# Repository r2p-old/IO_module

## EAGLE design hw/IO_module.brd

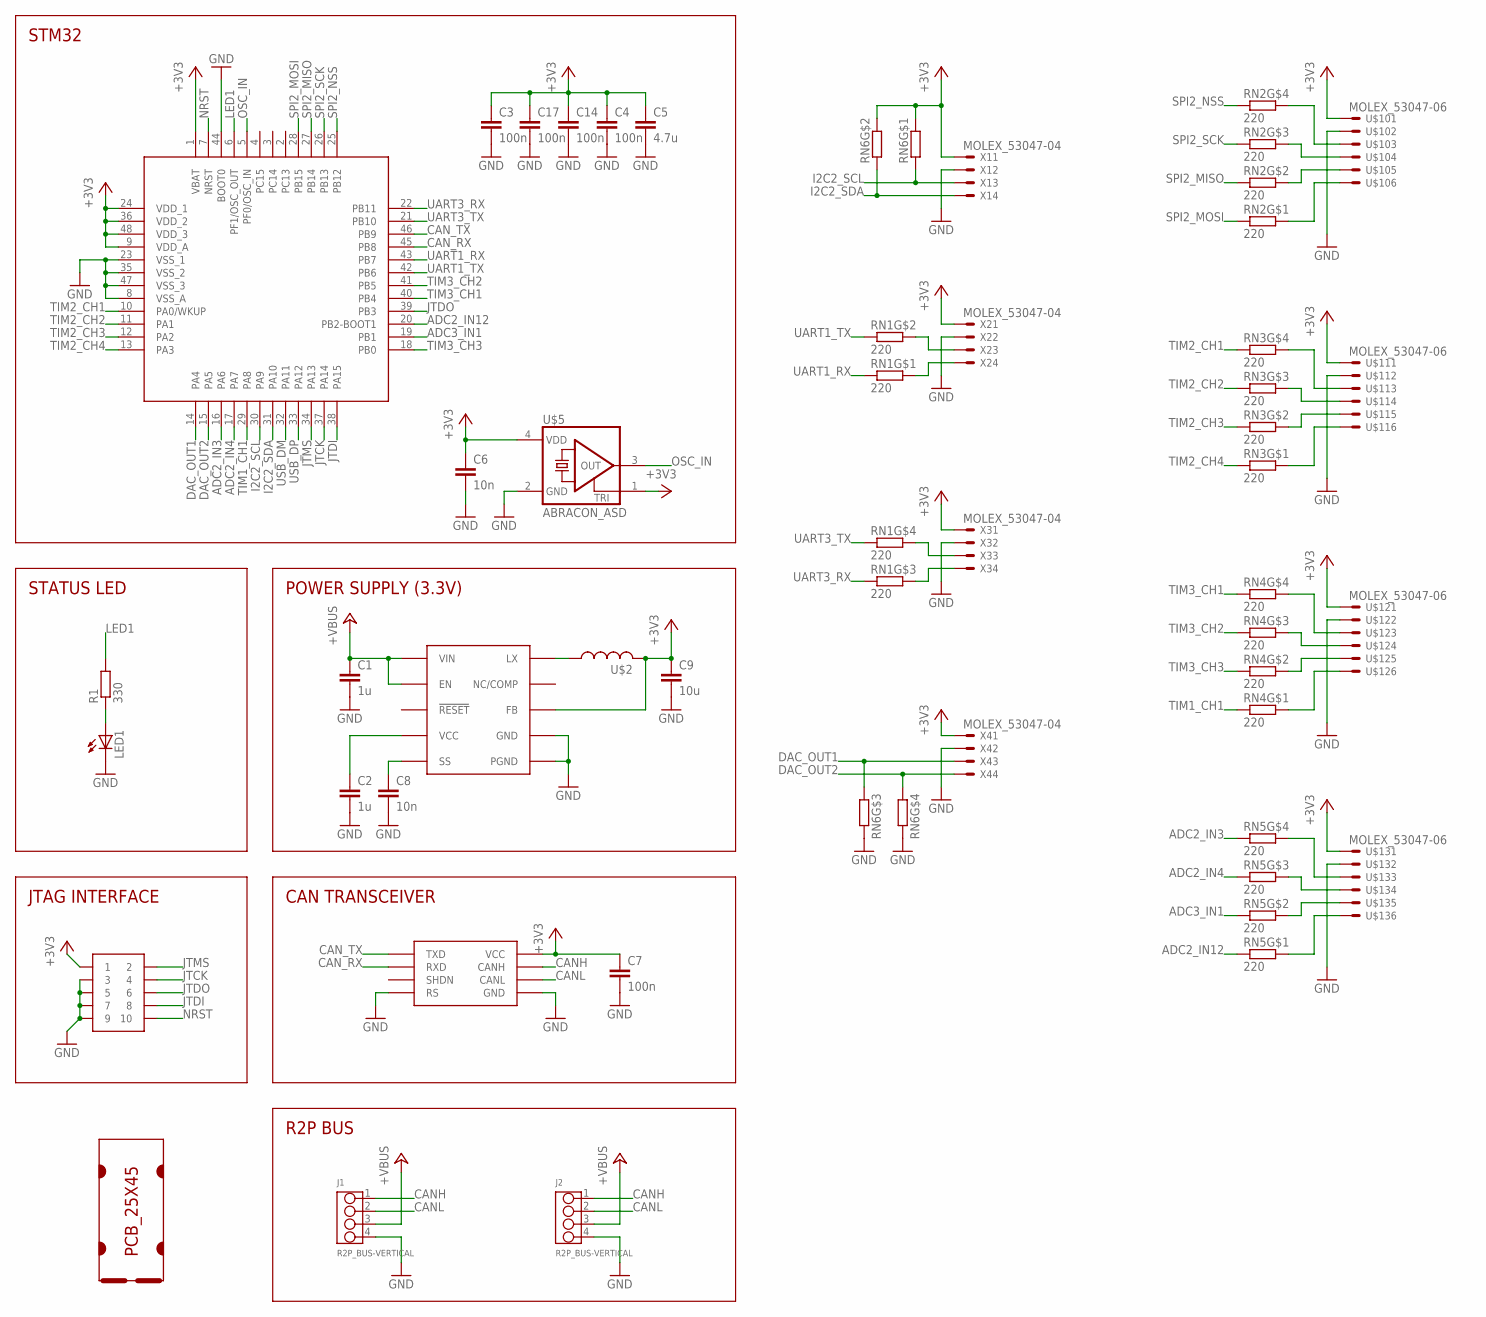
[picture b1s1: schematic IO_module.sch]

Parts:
C1: 1u; C1206
C2: 1u; C0603
C3, C4, C7, C14, C17: 100n; C0603
C5: 4.7u; C0805
C6, C8: 10n; C0603
C9: 10u; C0805
J1, J2: R2P_BUS-VERTICAL; OPL-EAGLE-LIBRARY_4P-2.0
LED1: LED0805; CHIPLED_0805
R1: 330; R0603
RN1, RN2, RN3, RN4, RN5: 220; RNET4_1206
RN6: RNETWORK_4-1206; RNET4_1206
SOT1: MAX3051EKA; SOT23-8L
U$1: PCB_25X45; 25X45
U$2: LPS4018; COILCRAFT_LPS4018
U$3: MAX17501; TDFN-10
U$4: JTAG-TH; SAMTEC_FTSH-105-TH
U$5: ABRACON_ASD; ABRACON_2.5X2
U$6: STM32F303CTX; LQFP48
U$10, U$11, U$12, U$13: MOLEX_53047-06
X1, X2, X3, X4: MOLEX_53047-04

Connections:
+3V3: C3.1, C4.1, C5.1, C6.1, C7.1, C9.1, C14.1, C17.1, RN6.7 (2), RN6.8 (2), SOT1.3 (VCC), U$2.P$2 (2), U$3.P$5 (FB), U$4.1, U$5.1 (TRI), U$5.4 (VDD), U$6.1 (VBAT), U$6.9 (VDD_A), U$6.24 (VDD_1), U$6.36 (VDD_2), U$6.48 (VDD_3), U$10.1, U$11.1, U$12.1, U$13.1, X1.1, X2.1, X3.1, X4.1
+VBUS: C1.1, J1.3, J2.3, U$3.P$2 (VIN), U$3.P$3 (EN)
ADC2_IN3: RN5.4 (1), U$6.16 (PA6)
ADC2_IN4: RN5.3 (1), U$6.17 (PA7)
ADC2_IN12: RN5.1, U$6.20 (PB2-BOOT1)
ADC3_IN1: RN5.2 (1), U$6.19 (PB1)
CANH: J1.1, J2.1, SOT1.7 (CANH)
CANL: J1.2, J2.2, SOT1.6 (CANL)
CAN_RX: SOT1.4 (RXD), U$6.45 (PB8)
CAN_TX: SOT1.1 (TXD), U$6.46 (PB9)
DAC_OUT1: RN6.3 (1), U$6.14 (PA4), X4.3
DAC_OUT2: RN6.4 (1), U$6.15 (PA5), X4.4
GND: C1.2, C2.2, C3.2, C4.2, C5.2, C6.2, C7.2, C8.2, C9.2, C14.2, C17.2, J1.4, J2.4, LED1.C, RN6.5 (2), RN6.6 (2), SOT1.2 (GND), SOT1.8 (RS), U$3.P$1 (PGND), U$3.P$9 (GND), U$3.P$11 (PGND), U$4.3, U$4.5, U$4.7, U$4.9, U$5.2 (GND), U$6.8 (VSS_A), U$6.23 (VSS_1), U$6.35 (VSS_2), U$6.44 (BOOT0), U$6.47 (VSS_3), U$10.2, U$11.2, U$12.2, U$13.2, X1.2, X2.2, X3.2, X4.2
I2C2_SCL: RN6.1, U$6.30 (PA9), X1.3
I2C2_SDA: RN6.2 (1), U$6.31 (PA10), X1.4
JTCK: U$4.4, U$6.37 (PA14)
JTDI: U$4.8, U$6.38 (PA15)
JTDO: U$4.6, U$6.39 (PB3)
JTMS: U$4.2, U$6.34 (PA13)
LED1: R1.2, U$6.6 (PF1/OSC_OUT)
unnamed: U$2.P$1 (1), U$3.P$10 (LX)
unnamed: RN1.5 (2), X3.3
unnamed: LED1.A, R1.1
unnamed: RN1.7 (2), X2.3
unnamed: RN1.8 (2), X2.4
unnamed: C2.1, U$3.P$4 (VCC)
unnamed: C8.1, U$3.P$6 (SS)
unnamed: RN1.6 (2), X3.4
unnamed: RN2.8 (2), U$10.6
unnamed: RN2.7 (2), U$10.5
unnamed: RN2.6 (2), U$10.4
unnamed: RN2.5 (2), U$10.3
unnamed: RN5.8 (2), U$13.6
unnamed: RN5.7 (2), U$13.5
unnamed: RN5.6 (2), U$13.4
unnamed: RN5.5 (2), U$13.3
unnamed: RN4.5 (2), U$12.3
unnamed: RN4.6 (2), U$12.4
unnamed: RN4.7 (2), U$12.5
unnamed: RN4.8 (2), U$12.6
unnamed: RN3.5 (2), U$11.3
unnamed: RN3.6 (2), U$11.4
unnamed: RN3.7 (2), U$11.5
unnamed: RN3.8 (2), U$11.6
NRST: U$4.10, U$6.7 (NRST)
OSC_IN: U$5.3 (OUT), U$6.5 (PF0/OSC_IN)
SPI2_MISO: RN2.2 (1), U$6.27 (PB14)
SPI2_MOSI: RN2.1, U$6.28 (PB15)
SPI2_NSS: RN2.4 (1), U$6.25 (PB12)
SPI2_SCK: RN2.3 (1), U$6.26 (PB13)
TIM1_CH1: RN4.1, U$6.29 (PA8)
TIM2_CH1: RN3.4 (1), U$6.10 (PA0/WKUP)
TIM2_CH2: RN3.3 (1), U$6.11 (PA1)
TIM2_CH3: RN3.2 (1), U$6.12 (PA2)
TIM2_CH4: RN3.1, U$6.13 (PA3)
TIM3_CH1: RN4.4 (1), U$6.40 (PB4)
TIM3_CH2: RN4.3 (1), U$6.41 (PB5)
TIM3_CH3: RN4.2 (1), U$6.18 (PB0)
UART1_RX: RN1.1, U$6.43 (PB7)
UART1_TX: RN1.2 (1), U$6.42 (PB6)
UART3_RX: RN1.3 (1), U$6.22 (PB11)
UART3_TX: RN1.4 (1), U$6.21 (PB10)
USB_DM: U$6.32 (PA11)
USB_DP: U$6.33 (PA12)

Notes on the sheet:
STM32
STATUS LED
JTAG INTERFACE
POWER SUPPLY (3.3V)
CAN TRANSCEIVER
R2P BUS

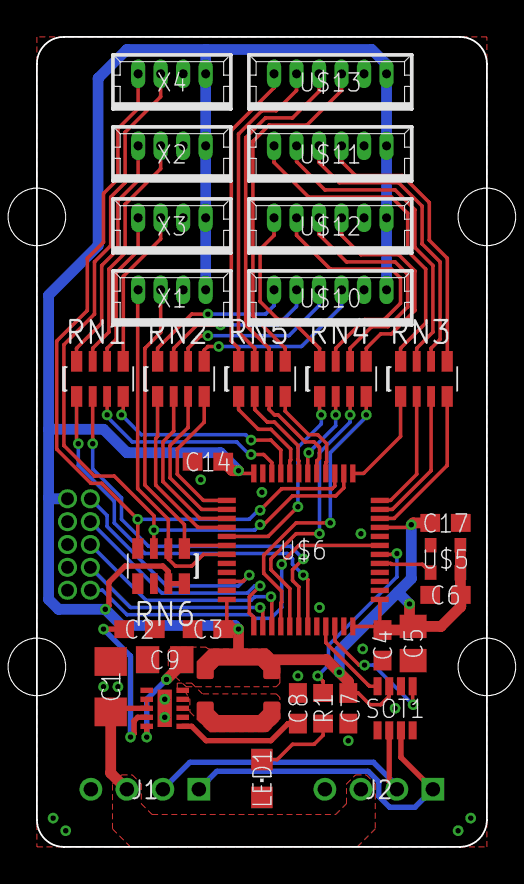
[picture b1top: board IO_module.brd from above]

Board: 2 copper layers, 25.0 x 45.0 mm, 36 parts (0 on the bottom side), 62 nets.

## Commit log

2015-02-07 Layout complete
2015-02-09 Updated keepout
2015-02-19 Fixed directory creation
2015-02-19 Fixed silkscreen
